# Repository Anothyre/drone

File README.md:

# HTL - drone project 2025

some confused guys building a drone (IFO) drom scratch

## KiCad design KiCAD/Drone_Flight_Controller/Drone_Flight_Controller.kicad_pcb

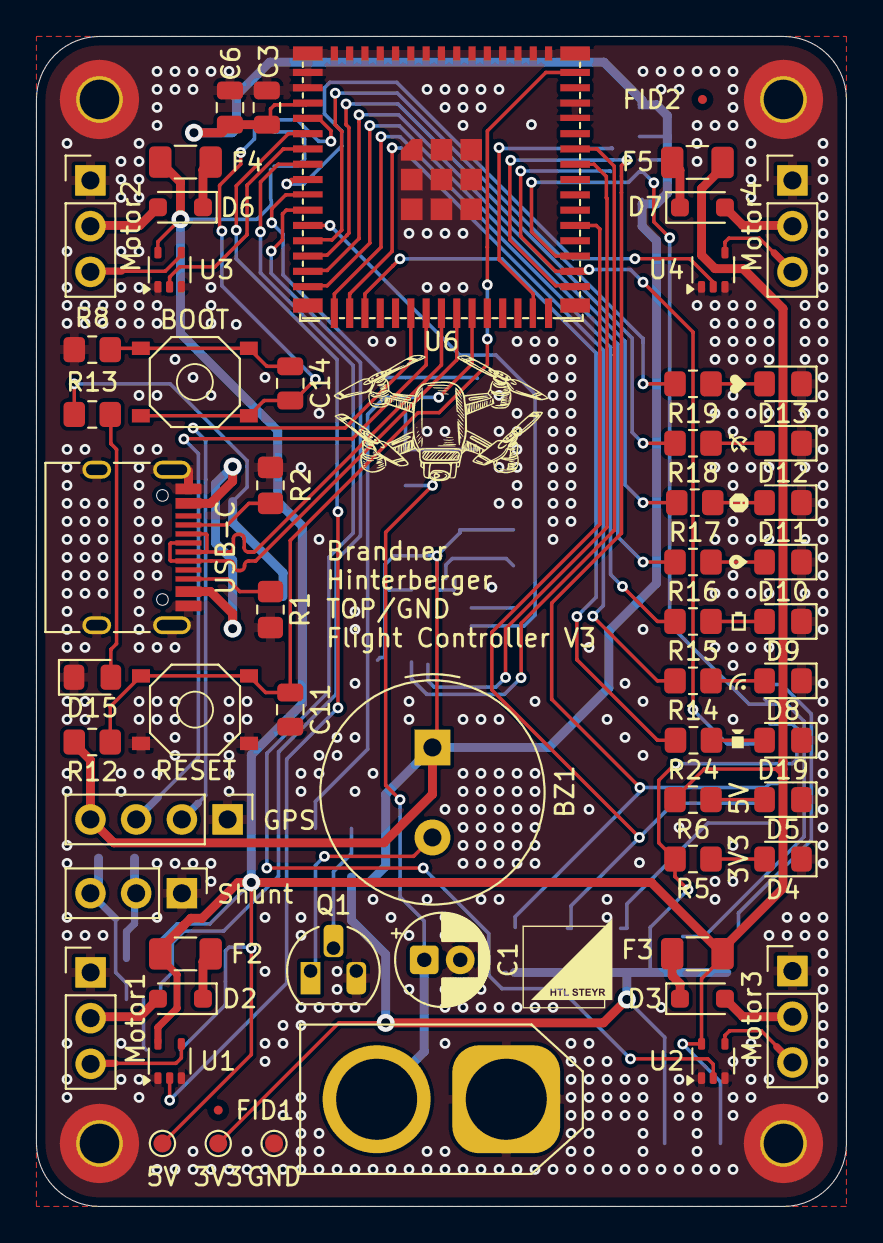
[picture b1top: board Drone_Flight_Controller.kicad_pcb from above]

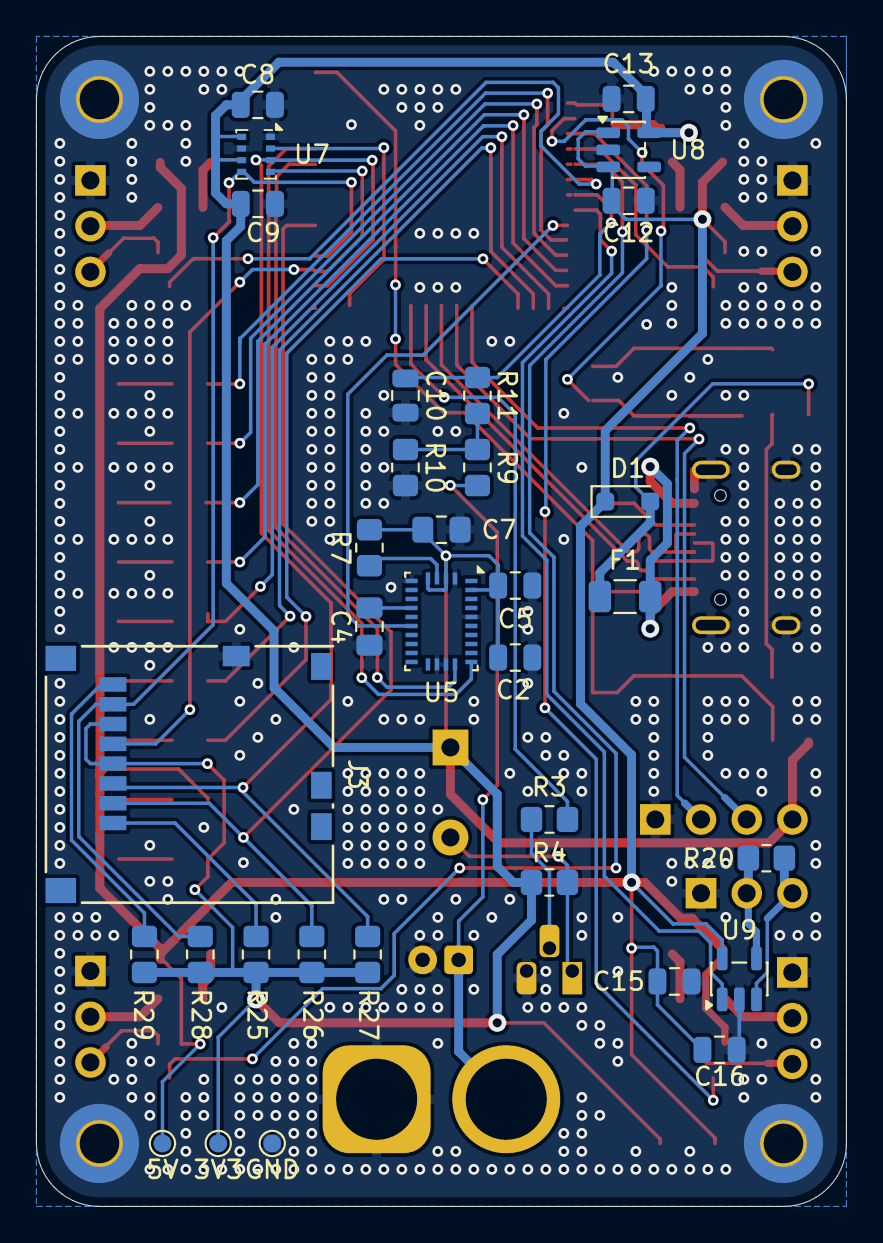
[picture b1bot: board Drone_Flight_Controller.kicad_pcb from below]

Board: 2 copper layers, 45.0 x 65.0 mm, 97 parts (33 on the bottom side), 68 nets.

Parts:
3V3, 3V3#2: 3V3; TestPoint_Pad_D1.0mm
5V, 5V#2: +5V; TestPoint_Pad_D1.0mm
BZ1: Buzzer; Buzzer_TDK_PS1240P02BT_D12.2mm_H6.5mm
C1: 22u; CP_Radial_D5.0mm_P2.00mm
C2, C6, C9, C10, C11, C14, C16: 100nF; C_0805_2012Metric
C3, C5, C8, C12, C13, C15: 10uF; C_0805_2012Metric
C4: 1uF; C_0805_2012Metric_Pad1.18x1.45mm_HandSolder
C7: 120n; C_0805_2012Metric_Pad1.18x1.45mm_HandSolder
D1, D2, D3, D6, D7: BAT60BE6359HTMA1; D_SOD-323_HandSoldering
D4, D5, D8, D9, D10, D11, D12, D13, D15, D19: LED; LED_0805_2012Metric_Pad1.15x1.40mm_HandSolder
F1, F2, F3, F4, F5: PTS12066V050; Fuse_1206_3216Metric
FID1, FID2: Fiducial; Fiducial_0.5mm_Mask1mm
G1: Logo_HTL_Steyr_Small; HTL-Steyr-Logo_5mm_Copper
GND: GND; TestPoint_Pad_D1.0mm
GND#2: GND; TestPoint_Pad_D1.0mm
GPS: Conn_01x04; PinHeader_1x04_P2.54mm_Vertical
H1, H2, H3, H4: MountingHole_Pad; MountingHole_2.2mm_M2_Pad_TopBottom
J1: XT60; AMASS_XT60-F_1x02_P7.20mm_Vertical
J3: Micro_SD_Card; 502570-0893_MOL
Motor1, Motor2, Motor3, Motor4: Conn_01x03; PinHeader_1x03_P2.54mm_Vertical
Q1: 2N2222A; TO-92_HandSolder
R1, R2: 5k1; R_0805_2012Metric_Pad1.20x1.40mm_HandSolder
R3: 180; R_0805_2012Metric_Pad1.20x1.40mm_HandSolder
R4: 1k; R_0805_2012Metric_Pad1.20x1.40mm_HandSolder
R5, R14, R15, R16, R17, R18, R19, R24: 1k8; R_0805_2012Metric_Pad1.20x1.40mm_HandSolder
R6, R13: 3k6; R_0805_2012Metric_Pad1.20x1.40mm_HandSolder
R7, R8, R10, R12, R25, R26, R27, R28, R29: 10k; R_0805_2012Metric_Pad1.20x1.40mm_HandSolder
R9: 43k; R_0805_2012Metric_Pad1.20x1.40mm_HandSolder
R11: 220; R_0805_2012Metric_Pad1.20x1.40mm_HandSolder
R20: 24; R_0805_2012Metric_Pad1.20x1.40mm_HandSolder
SW1, SW2: SW_Push; SW_Push_5.1mm_H1.5mm
Shunt: Conn_01x03; PinHeader_1x03_P2.54mm_Vertical
U1, U2, U3, U4: 74AHC1G125; SOT-353_SC-70-5
U5: BNO055; LGA-28_5.2x3.8mm_P0.5mm
U6: ESP32-S3-MINI-1
U7: DPS368; Bosch_LGA-8_2x2.5mm_P0.65mm_ClockwisePinNumbering
U8: TLV75533PDBV; SOT-23-5
U9: INA195; SOT-23-5
USB-C: USB_C_Receptacle_USB2.0_14P; USB_C_Receptacle_HRO_TYPE-C-31-M-12

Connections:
+3V3: 3V3.1, 3V3#2.1, BZ1.1 (+), C2.1, C3.1, C5.1, C6.1, C7.1, C8.1, C9.1, C13.1, GPS.4, J3.4 (VDD), J3.6 (VSS), R4.1, R5.1, R7.2, R12.1, R25.1, R26.1, R27.1, R28.1, R29.1, U5.3 (VDD), U5.5 (PS1), U5.28 (VDDIO), U6.3 (3V3), U7.6 (VDDIO), U7.8 (VDD), U8.5 (OUT)
+5V: 5V.1, 5V#2.1, C12.1, C15.1, C16.1, D1.1 (K), F2.2, F3.2, F4.2, F5.2, R6.1, U1.5 (VCC), U2.5 (VCC), U3.5 (VCC), U4.5 (VCC), U8.1 (IN), U8.3 (EN), U9.5 (V+)
+BATT: C1.1, J1.2, R9.1
BATT Monitor: C10.1, R11.2, U6.9 (GPIO5/TOUCH5/ADC1_CH4)
Buzzer: R3.1, U6.25 (GPIO21)
CurrentSense: U6.10 (GPIO6/TOUCH6/ADC1_CH5), U9.1
D+: U6.24 (GPIO20/U1CTS/ADC2_CH9/CLK_OUT1/USB_D+), USB-C.A6 (D+), USB-C.B6 (D+)
D-: U6.23 (GPIO19/U1RTS/ADC2_CH8/CLK_OUT2/USB_D-), USB-C.A7 (D-), USB-C.B7 (D-)
DPS368 ~CS: U6.29 (SPIIO5/GPIO34/FSPICS0/SUBSPICS0), U7.2 (~CS)
EN: C11.1, R12.2, SW2.2, U6.45 (EN)
GND: C1.2, C2.2, C3.2, C4.2, C5.2, C6.2, C7.2, C8.2, C9.2, C10.2, C11.2, C12.2, C13.2, C15.2, C16.2, D4.1 (K), D5.1 (K), D8.1 (K), D9.1 (K), D10.1 (K), D11.1 (K), D12.1 (K), D13.1 (K), D15.1 (K), D19.1 (K), GND.1, GND#2.1, GPS.1, H1.1, H2.1, H3.1, H4.1, J1.1, J3.9 (SHIELD), Motor1.1, Motor2.1, Motor3.1, Motor4.1, Q1.3 (E), R1.2, R2.2, R8.2, R10.2, SW2.1, Shunt.1, U1.1, U1.3 (GND), U2.1, U2.3 (GND), U3.1, U3.3 (GND), U4.1, U4.3 (GND), U5.2 (GND), U5.6 (PS0), U5.17 (COM3), U5.18 (COM2), U5.25 (GNDIO), U6.1 (GND), U6.2 (GND), U6.42 (GND), U6.43 (GND), U6.46 (GND), U6.47 (GND), U6.48 (GND), U6.49 (GND), U6.50 (GND), U6.51 (GND), U6.52 (GND), U6.53 (GND), U6.54 (GND), U6.55 (GND), U6.56 (GND), U6.57 (GND), U6.58 (GND), U6.59 (GND), U6.60 (GND), U6.61 (GND), U6.62 (GND), U6.63 (GND), U6.64 (GND), U6.65 (GND), U7.1 (GND), U7.7 (GND), U8.2 (GND), U9.2 (GND), USB-C.A1 (GND), USB-C.A12 (GND), USB-C.B1 (GND), USB-C.B12 (GND), USB-C.S1 (SHIELD)
GPS RX: GPS.2, U6.21 (GPIO17/U1TXD/ADC2_CH6)
GPS TX: GPS.3, U6.22 (GPIO18/U1RXD/ADC2_CH7/CLK_OUT3)
IMU RX: U5.19 (COM1), U6.39 (U0TXD/GPIO43/CLK_OUT1)
IMU TX: U5.20 (COM0), U6.40 (U0RXD/GPIO44/CLK_OUT2)
IMU ~BOOT_LOAD_PIN: R7.1, U5.4 (~BOOT_LOAD_PIN)
IMU ~RESET: U5.11 (~RESET), U6.11 (GPIO7/TOUCH7/ADC1_CH6)
LED1: R19.1, U6.12 (GPIO8/TOUCH8/ADC1_CH7/SUBSPICS1)
LED2: R18.1, U6.13 (GPIO9/TOUCH9/ADC1_CH8/FSPIHD/SUBSPIHD)
LED3: R17.1, U6.14 (GPIO10/TOUCH10/ADC1_CH9/FSPICS0/FSPIIO4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)
LED4: R16.1, U6.15 (GPIO11/TOUCH11/ADC2_CH0/FSPID/FSPIIO5/S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)
LED5: R15.1, U6.16 (GPIO12/TOUCH12/ADC2_CH1/FSPICLK/FSPIIO6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)
LED6: R14.1, U6.17 (GPIO13/TOUCH13/ADC2_CH2/FSPIQ/FSPIIO7/S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)
LED7: R24.1, U6.18 (GPIO14/TOUCH14/ADC2_CH3/FSPIWP/FSPIDQS/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)
Motor1: U1.2, U6.5 (GPIO1/TOUCH1/ADC1_CH0)
Motor2: U3.2, U6.6 (GPIO2/TOUCH2/ADC1_CH1)
Motor3: U2.2, U6.7 (GPIO3/TOUCH3/ADC1_CH2)
Motor4: U4.2, U6.8 (GPIO4/TOUCH4/ADC1_CH3)
unnamed: BZ1.2 (-), Q1.1 (C), R4.2
unnamed: C14.1, R8.1, SW1.2
unnamed: D1.2 (A), F1.2, R13.1
unnamed: D2.2 (A), Motor1.2
unnamed: D2.1 (K), F2.1
unnamed: D3.2 (A), Motor3.2
unnamed: D3.1 (K), F3.1
unnamed: D4.2 (A), R5.2
unnamed: D5.2 (A), R6.2
unnamed: D6.2 (A), Motor2.2
unnamed: D6.1 (K), F4.1
unnamed: D7.2 (A), Motor4.2
unnamed: D7.1 (K), F5.1
unnamed: D8.2 (A), R14.2
unnamed: D9.2 (A), R15.2
unnamed: D10.2 (A), R16.2
unnamed: D11.2 (A), R17.2
unnamed: D12.2 (A), R18.2
unnamed: D13.2 (A), R19.2
unnamed: D15.2 (A), R13.2
unnamed: D19.2 (A), R24.2
unnamed: F1.1, USB-C.A4 (VBUS), USB-C.A9 (VBUS), USB-C.B4 (VBUS), USB-C.B9 (VBUS)
unnamed: R20.2, Shunt.2, U9.4 (-)
unnamed: R20.1, Shunt.3, U9.3 (+)
unnamed: J3.8 (DAT1), R29.2
unnamed: J3.1 (DAT2), R25.2
unnamed: Motor1.3, U1.4
unnamed: Motor2.3, U3.4
unnamed: Motor3.3, U2.4
unnamed: Motor4.3, U4.4
unnamed: Q1.2 (B), R3.2
unnamed: R9.2, R10.1, R11.1
unnamed: C4.1, U5.9 (CAP)
unnamed: C14.2, SW1.1, U6.4 (GPIO0/BOOT)
unnamed: R2.1, USB-C.A5 (CC1)
unnamed: R1.1, USB-C.B5 (CC2)
SCK: J3.5 (CLK), U6.32 (SPIIO7/GPIO36/FSPICLK/SUBSPICLK), U7.4 (SCK)
SDI: J3.3 (CMD), R27.2, U6.31 (SPIIO6/GPIO35/FSPID/SUBSPID), U7.3 (SDI)
SDO: J3.7 (DAT0), R28.2, U6.33 (SPIDQS/GPIO37/FSPIQ/SUBSPIQ), U7.5 (SDO)
SD_CS: J3.2 (DAT3/CD), R26.2, U6.35 (MTCK/GPIO39/CLK_OUT3/SUBSPICS1)

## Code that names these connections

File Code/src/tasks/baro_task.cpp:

#include <Arduino.h>
#include "tasks/baro_task.h"
#include "shared.h"
#include "data_structures.h"
#include <SPI.h>
#include <cmath>
#include <freertos/FreeRTOS.h>
#include <freertos/task.h>

const float DroneBaro::SEA_LEVEL_PRESSURE = 101325.0f;



const int BARO_CS_PIN   = 34;  // Chip Select  (GPIO34)
const int BARO_CLK_PIN  = 36;  // Clock        (GPIO36)
const int BARO_MOSI_PIN = 35;  // MOSI / SDI   (GPIO35)
const int BARO_MISO_PIN = 37;  // MISO / SDO   (GPIO37)
const int BARO_INT_PIN  = -1;  // Not wired — DPS368 has no INT line in 4-wire SPI

const uint16_t BARO_TASK_STACK_SIZE = 4096;
const int BARO_TASK_PRIORITY = 5;
const uint32_t BARO_UPDATE_RATE_MS = 50;

DroneBaro::DroneBaro(int csPin, int intPin, SPIClass &spiBus)
    : _csPin(csPin), _intPin(intPin), _spi(spiBus)
{
    memset(&_data, 0, sizeof(_data));
    _pressureOS = DPS368_OS_16X;
    _pressureRate = DPS368_RATE_64HZ;
    _tempOS = DPS368_OS_2X;
    _tempRate = DPS368_RATE_4HZ;
}

bool DroneBaro::init(
    DPS368_SamplingRate pressureRate,
    DPS368_Oversampling pressureOS,
    DPS368_SamplingRate tempRate,
    DPS368_Oversampling tempOS,
    DPS368_MeasurementMode mode)
{
    _pressureRate = pressureRate;
    _pressureOS = pressureOS;
    _tempRate = tempRate;
    _tempOS = tempOS;
    _dataReady = false;

    if (BARO_CS_PIN == BARO_MISO_PIN) {
        Serial.println("[BARO] ERROR: BARO_CS_PIN and BARO_MISO_PIN are both set to GPIO37.");
        Serial.println("[BARO] Fix the wiring/pin config before SPI barometer access can work.");
        return false;
    }

    pinMode(_csPin, OUTPUT);
    digitalWrite(_csPin, HIGH);
    if (_intPin != -1) {
        pinMode(_intPin, INPUT);
    }

    _spi.begin(BARO_CLK_PIN, BARO_MISO_PIN, BARO_MOSI_PIN, _csPin);
    _sensor.begin(_spi, _csPin);

    if (!startMeasurements(mode)) {
        Serial.println("[BARO] ERROR: Failed to start measurements");
        return false;
    }

    Serial.printf("[BARO] Initialized successfully (Product ID 0x%02X, Revision 0x%02X)\n",
                  _sensor.getProductId(),
                  _sensor.getRevisionId());
    return true;
}

bool DroneBaro::startMeasurements(DPS368_MeasurementMode mode)
{
    int16_t result = -1;

    switch (mode) {
        case DPS368_MODE_CONT_BOTH:
            result = _sensor.startMeasureBothCont(
                (uint8_t)_tempRate,
                (uint8_t)_tempOS,
                (uint8_t)_pressureRate,
                (uint8_t)_pressureOS);
            break;
        case DPS368_MODE_CONT_PRESSURE:
            result = _sensor.startMeasurePressureCont((uint8_t)_pressureRate, (uint8_t)_pressureOS);
            break;
        case DPS368_MODE_CONT_TEMP:
            result = _sensor.startMeasureTempCont((uint8_t)_tempRate, (uint8_t)_tempOS);
            break;
        case DPS368_MODE_IDLE:
            result = _sensor.standby();
            break;
        default:
            Serial.println("[BARO] ERROR: Command measurement modes are not used by TaskBaro");
            return false;
    }

    if (result != 0) {
        Serial.printf("[BARO] ERROR: Infineon library returned %d while starting measurements\n", result);
        return false;
    }

    return mode != DPS368_MODE_IDLE;
}

void DroneBaro::update()
{
    _dataReady = false;

    if (readMeasurement()) {
        calculateAltitude();
        _dataReady = true;

        BaroData baroMsg = {
            _data.pressure_pa,
            _data.temperature_degc,
            _data.altitude_m
        };
        xQueueOverwrite(baroQueue, &baroMsg);
    }
}

bool DroneBaro::readMeasurement()
{
    float tempBuffer[8];
    float pressureBuffer[8];
    uint8_t tempCount = 8;
    uint8_t pressureCount = 8;

    int16_t result = _sensor.getContResults(tempBuffer, tempCount, pressureBuffer, pressureCount);
    if (result != 0) {
        Serial.printf("[BARO] WARN: Infineon library returned %d while reading\n", result);
        return false;
    }

    if (tempCount == 0 || pressureCount == 0) {
        return false;
    }

    _data.temperature_degc = tempBuffer[tempCount - 1];
    _data.pressure_pa = pressureBuffer[pressureCount - 1];
    return true;
}

void DroneBaro::calculateAltitude()
{
    float pressureRatio = _data.pressure_pa / SEA_LEVEL_PRESSURE;

    if (pressureRatio > 0.0f) {
        _data.altitude_m = 44330.0f * (1.0f - powf(pressureRatio, 0.1902949f));
    } else {
        _data.altitude_m = 0.0f;
    }
}

void DroneBaro::printCalibrationData() const
{
    Serial.println("[BARO] Calibration coefficients are managed by the Infineon DPS310 library.");
}

void TaskBaro(void *pvParameters)
{
    DroneBaro barometer(BARO_CS_PIN, BARO_INT_PIN, SPI);

    if (!barometer.init(
        DPS368_RATE_64HZ,
        DPS368_OS_16X,
        DPS368_RATE_4HZ,
        DPS368_OS_2X,
        DPS368_MODE_CONT_BOTH
    )) {
        Serial.println("[TaskBaro] Initialization failed!");
        vTaskDelete(nullptr);
        return;
    }

    TickType_t xLastWakeTime = xTaskGetTickCount();
    const TickType_t xFrequency = pdMS_TO_TICKS(BARO_UPDATE_RATE_MS);

    Serial.println("[TaskBaro] Task started, 20Hz update rate");

    for (;;) {
        barometer.update();

        if (barometer.isDataReady()) {
            const DPS368_Data &data = barometer.getData();
            Serial.printf("[BARO] P=%.0f Pa, T=%.1f C, Alt=%.1f m\n",
                          data.pressure_pa,
                          data.temperature_degc,
                          data.altitude_m);
        }

        vTaskDelayUntil(&xLastWakeTime, xFrequency);
    }
}

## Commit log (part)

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2025-06-26 Add .gitignore
    Add .gitignore
2025-06-26 Update .gitignor for KiCAC Project
    Update .gitignor for KiCAC Project
2025-06-26 Select components for IMU and Altimeter
    Select components for IMU and Altimeter
2025-06-30 Add buzzer and ESP32 symbol. Add Link to components to BOM. Add Names and company to title block.
    Add buzzer and ESP32 symbol.
    Add Link to components to BOM.
    Add Names and company to title block.
2025-07-02 add logo
    add Drone_Flight_Controller.kicad_sym
2025-07-02 Add 14.8V to 3.3V Converter
    Add 14.8V to 3.3V Converter
2025-07-02 Add Connectors & Power
    Add Connectors & Power
2025-07-02 Add Hierarchical Sheets
    Add Hierarchical Sheets
2025-07-02 Add Buzzer
    Add Buzzer
2025-07-02 Add uC and sensors
    Add uC and sensors
2025-07-02 Fix Bugs
    Fix Bugs
2025-07-02 Add ~* to .gitignore
    Add ~* to .gitignore
2025-07-02 Solve Errors
    Solve Errors
2025-07-07 Add Battery Monitoring
    Add Battery Monitoring
2025-07-07 Change +14.8V & GND to +BATT & -BATT
    Change +14.8V& GND to +BATT & -BATT
2025-07-13 Add Components to BOM
    Add Components to BOM
2025-07-13 Add USB & Status LEDS
    Add USB & Status LEDS
2025-07-13 Move USB to USB & Status LEDs. Add ESC Drive circuits
    Move USB to USB & Status LEDs. Add ESC Drive circuits
2025-07-13 Add Programming
    Add Programming
2025-07-13 Add ERC exceptions
    Add ERC exceptions
2025-07-13 Reannotate
    Reannotate
2025-07-13 Fix Footprint Error
    Fix Footprint Error
2025-07-13 Fix Label Error
    Fix Label Error
2025-07-13 Reanotate
    Reanotate
2025-07-13 Set Netclasses
    Set Netclasses
2025-07-13 Fix Bypass Capacitor error
    Fix Bypass Capacitor error
2025-07-13 Place Footprints
    Place Footprints
2025-07-13 Remove wrong 3D Model
    Remove wrong 3D Model
2025-07-13 Export STL File
    Export STL File
2025-07-13 Copy from KiCad
    Copy from KiCad
2025-07-17 Fix GPS RX/TX mixup
    Fix GPS RX/TX mixup
2025-07-17 Add Footprint to NetTie
    Add Footprint to NetTie
2025-07-17 Routing
    Routing
2025-07-17 Add Exceptions
    Add Exceptions
2025-07-17 Fix Errors Add Silkscreen
    Fix Errors Add Silkscreen
2025-07-17 Add Exceptions to DRC
    Add Exceptions to DRC
2025-07-17 Change Transistors to SMD Variants
    Change Transistors to SMD Variants
2025-07-18 Fix errors
    Fix errors
2025-07-18 Add Unity gain Amp to Battery Monitor
    Add Unity Gain Amp to Battery Monitor
2025-07-18 Export Updated PCB to STL
    Export Updated PCB to STL
2025-07-20 Export BOM
    Export BOM
2025-07-20 Export Gerber Files
    Export Gerber Files
2025-09-11 Export interactive HTML BOM via same named Plugin
    Export interactive HTML BOM via same named Plugin
2025-09-12 Add 5V_to_3.3V_Voltage_Converter.kicad_sch
2025-09-12 Fix Typo
2025-09-12 Add +4V76 via BEC circuits and USB
2025-09-12 Change filname inline with convention
2025-09-12 Change 5V to 4V76
2025-09-12 Expose 3 GPIO Pins
2025-09-15 Add safety resistor to programming pin
2025-09-16 Fix SPI Connection, Disconnect wrong UART connection
2025-09-18 Connect IMU via UART by IOMUX
2025-09-18 Remove unused connector
2025-09-18 Fix date
2025-09-18 Fix ESC drivers
2025-09-18 Fix error in Commit 28fc275 because of not saving
2025-09-19 Add power indicator LEDs
2025-09-19 Add IO connector
2025-09-19 Remove 14.8V to 3.3V Voltage Converter
2025-09-19 Reannotate
2025-09-19 Copy footprints to new parts
2025-09-19 Change "+3.3V" to "+3V3" for consistency
2025-09-19 Fix references
2025-09-19 Rename connectors to Motor[1..4]
2025-09-19 Change footprints to HandSoldering
2025-09-19 Remove unneaded OPAMPs
2025-09-19 Preliminary fotprint placement
2025-09-19 add footprint of USB C connector
    add footprint of USB C connector
2025-09-20 Change to 2-sided assembly
2025-09-20 Remove battery LED for power draw reasons
2025-09-20 Fix wrongly excluded component
2025-09-20 Add footprints for LED protection resistors
2025-09-20 part placement and routing
    part placement and routing
2025-09-21 Fix errors
2025-09-21 extend board length
    extend board length
2025-09-22 Fixing errors
    Fixing errors
2025-09-27 Remove unneeded Capacitors
2025-09-27 Fix USB-C Symbol
2025-09-27 Update date
2025-09-27 Move .gitignore
2025-09-27 Fix Schematic PCB parity
2025-09-27 Fix DRC Errors
2025-09-29 bottom GND and USB C port
2025-10-02 Add 470µ Capacitors to ESCs and 4V76
2025-10-02 Add 10µ Capacitors to ESCs
2025-10-02 Add 100n Capacitors to ESCs
2025-10-08 add IFO picture and HTL Logo
    add IFO picture and HTL Logo
2025-10-13 Add TVS Diodes to 5V
2025-10-14 Connector and ESP placement
    Connector and ESP placement
2025-10-15 diodes
    add diodes
2025-10-15 solve routing errors
    solve routing errors
2025-10-19 improving routing
    improving routing
2025-10-19 routing
2025-10-27 Fix Bugs
2025-10-27 Add Viastiching
2025-11-05 add capacitor
    add capacitor
2025-11-06 Remove extraneous Cs
2025-11-06 Cleanup
2025-11-06 Cleanup & Re-annotate
2025-11-06 Re-annotate
2025-11-06 add USB C resistors
2025-11-10 Add ESP hole size change to exclusions
2025-11-10 Fix warnigns
2025-11-10 Update Transistor Footprints
2025-11-10 Update Exclusions
2025-11-10 Update footprints
2025-11-10 Remove Silkcreen from outside Board. Again
2025-11-10 Update Footprints. again.
2025-11-10 Fix Warnings
2025-11-10 Fix USB-C Collistion
2025-11-12 Create new project
2025-11-12 Revision 3
2025-11-17 Add Status LEDs
2025-11-20 Fix Error with Motors
2025-11-21 Add Current and ESC sense
2025-11-24 Add ESC Sense
2025-11-24 Add Footprints.
2025-11-26 Implement feedback from Prof. Parzer
2025-11-26 Add µSD Card Holder
2025-11-26 Fix wrong footprint
2025-11-26 Add debouncing C to button
2025-11-26 Routing and placing
    Routing and placing
2025-11-26 Revision
2025-11-27 Add signage
2025-11-28 Shorten traces
2025-11-28 Update Signage
2025-11-28 Exclude wrong violations
2025-11-28 Mark GND on connectors
2025-11-28 Add resistor parallel to shunt to lower EMI
2025-11-29 Fix issues from merging
2025-12-01 silk screen
    silk screen
2025-12-01 Final Revision
2025-12-01 final final revision
    final final revision
2025-12-02 export GBR dater
    export GBR dater
2025-12-06 Create PlatformIO Project
2025-12-30 Add files via upload
    what we have done
2025-12-30 Add initial README for drone project 2025
2026-01-01 Change Project Settings
2026-01-01 Recommend PlatformIO
2026-01-01 Change framework to Arduino
2026-01-01 Design tasks
2026-01-02 PID controller design
2026-01-02 Other
2026-01-08 Bug fixes
2026-01-08 Changed to OO approach
2026-01-11 TaskControl scemetic and bug fixes
2026-01-12 Comments and minor changes
2026-01-15 Delta_T in Task Control
2026-01-16 Update control_task
2026-01-21 control design update
2026-01-22 baro design
2026-01-23 Small fixes
2026-01-23 Gemini Baro design
2026-01-23 Queues
2026-01-23 Test functions in main
2026-01-23 FSM from flowchart
2026-01-23 Small Changes
2026-01-23 Copilot baro
2026-01-24 Datasheets
2026-02-01 Base 44 based UI
2026-02-02 Fokus on getting things done
2026-02-11 Move documentation into the "docs" folder
2026-02-11 Add pinout
2026-02-11 Implement reading current and battery voltage with ADC
2026-02-11 Add ADC samples to ADCQueue
2026-02-14 Codex bodenstation
2026-02-14 moved boden.py
2026-02-14 wled main
2026-02-15 human update boden
2026-02-17 wled debug task
2026-02-24 Outline TODO
2026-03-08 Implement IMU Task
2026-04-10 Simulink
2026-04-10 rename auf base44 groundstation
2026-06-21 Using external libarys
2026-06-30 Buzzer Led Debug
2026-06-30 Motor working?
2026-06-30 Baro consts fix
2026-06-30 HardwareTask and Todo
2026-06-30 copiled restored my code
